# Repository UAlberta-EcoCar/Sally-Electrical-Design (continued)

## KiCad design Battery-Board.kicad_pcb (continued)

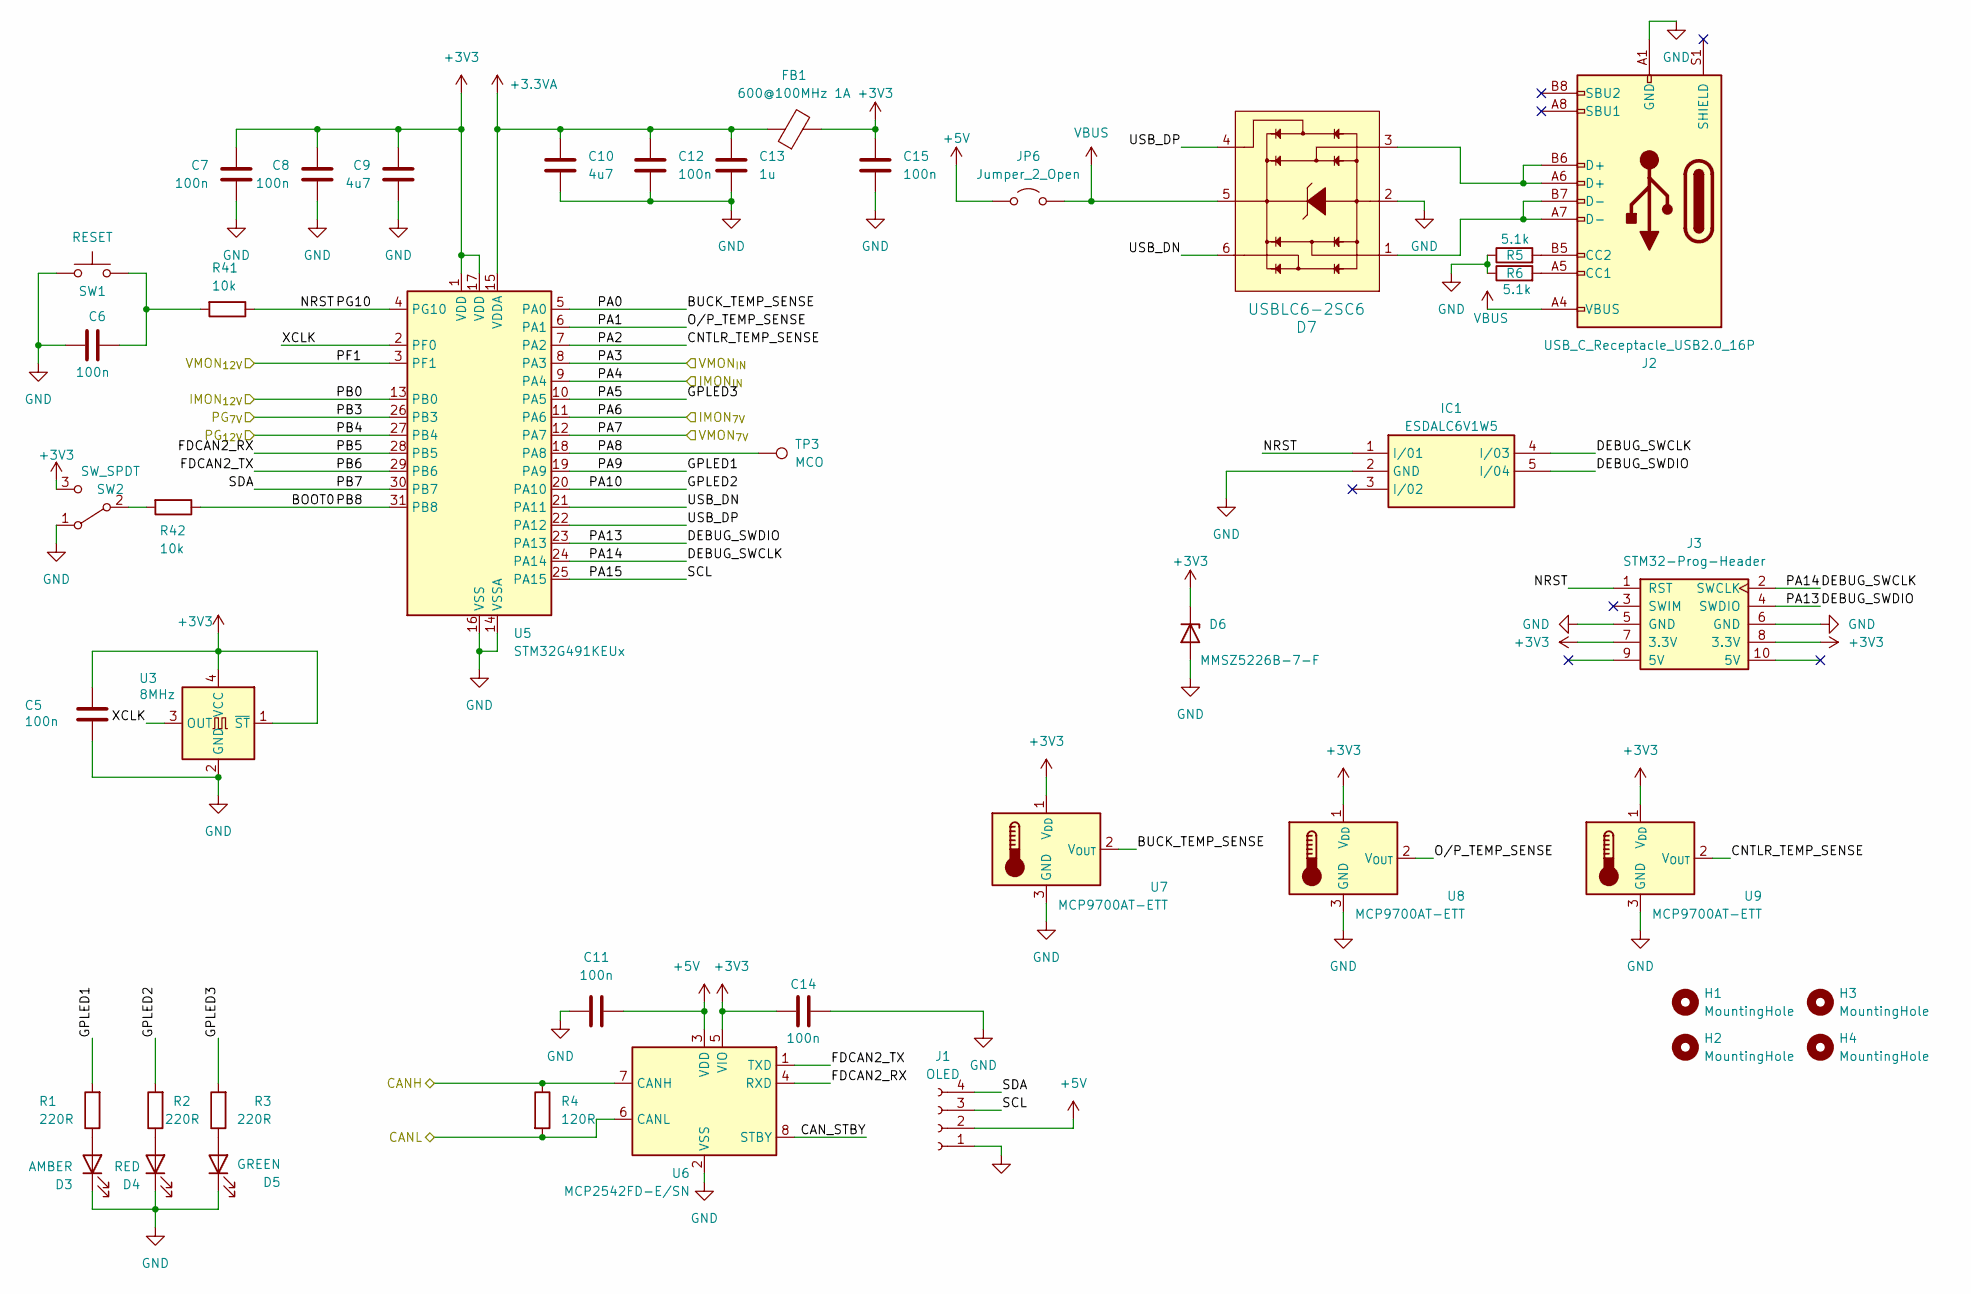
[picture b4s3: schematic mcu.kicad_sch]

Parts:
C5, C6, C11, C14: 100n; C_0603_1608Metric; JLCPCB Part#(Optional) C1525
C7, C8: 100n; C_0603_1608Metric
C9: 4u7; C_0805_2012Metric
C10: 4u7; C_0603_1608Metric; JLCPCB Part#(Optional) C96446
C12: 100n; C_0603_1608Metric; JLCPCB Part#(Optional) C96446
C13: 1u; C_0603_1608Metric; JLCPCB Part#(Optional) C28323
C15: 100n; C_0603_1608Metric; JLCPCB Part#(Optional) C28323
D3: AMBER; LED_0603_1608Metric; JLCPCB Part#(Optional) C2296
D4: RED; LED_0603_1608Metric; JLCPCB Part#(Optional) C84256
D5: GREEN; LED_0603_1608Metric; JLCPCB Part#(Optional) C2297
D6: MMSZ5226B-7-F; D_SOD-123; Digikey # MMSZ5226B-FDICT-ND
D7: USBLC6-2SC6; TSOT-23-6; Digikey # 497-5235-1-ND
FB1: 600@100MHz 1A; L_0603_1608Metric; Digikey # 1934-1474-1-ND
H1, H2, H3, H4: MountingHole; MountingHole_3.5mm
IC1: ESDALC6V1W5; SOT65P210X110-5N; JLCPCB Part#(Optional) C2827626
J1: OLED; Display_128x64_096_I2C
J2: USB_C_Receptacle_USB2.0_16P; USB_C_Receptacle_GCT_USB4105-xx-A_16P_TopMnt_Horizontal
J3: STM32-Prog-Header; PinHeader_2x05_P2.54mm_Vertical
JP6: Jumper_2_Open
R1, R2, R3: 220R; R_0603_1608Metric; JLCPCB Part#(Optional) C17557
R4: 120R; R_0603_1608Metric
R5, R6: 5.1k; R_0603_1608Metric; JLCPCB Part#(Optional) C17557
R41, R42: 10k; R_0603_1608Metric; JLCPCB Part#(Optional) C17557
SW1: RESET; SW_PUSH_6mm_H5mm
SW2: SW_SPDT; SW_SPDT_PCM12; Digikey # 2223-SLW-66527511-SMT-TRCT-ND
TP3: MCO; PinHeader_1x01_P2.54mm_Vertical
U3: 8MHz; Crystal_SMD_3225-4Pin_3.2x2.5mm; Digikey # 535-ASE-8.000MHZ-L-C-TCT-ND
U5: STM32G491KEUx; QFN-32-1EP_5x5mm_P0.5mm_EP3.45x3.45mm
U6: MCP2542FD-E/SN; SOIC-8_3.9x4.9mm_P1.27mm; Digikey # MCP2542FD-E/SN-ND
U7, U8, U9: MCP9700AT-ETT; SOT-23; LCSC# C42288

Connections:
+3.3VA: C10.1, C12.1, C13.1, FB1.1, U5.15 (VDDA)
+3V3: C5.2, C7.1, C8.1, C9.1, C14.2, C15.1, D6.1 (K), FB1.2, J3.7 (3.3V), J3.8 (3.3V), SW2.3 (C), U3.1 (~ST), U3.4 (VCC), U5.1 (VDD), U5.17 (VDD), U6.5 (VIO), U7.1 (V_{DD}), U8.1 (V_{DD}), U9.1 (V_{DD}); also elsewhere on the board
+5V: C11.2, J1.2, JP6.1 (A), U6.3 (VDD); also elsewhere on the board
/CANH: R4.1, U6.7 (CANH); also elsewhere on the board
/CANL: R4.2, U6.6 (CANL); also elsewhere on the board
/MCU and sensors/BUCK_TEMP_SENSE: U5.5 (PA0), U7.2 (V_{OUT})
/MCU and sensors/CAN_STBY: U6.8 (STBY)
/MCU and sensors/CNTLR_TEMP_SENSE: U5.7 (PA2), U9.2 (V_{OUT})
/MCU and sensors/DEBUG_SWCLK: IC1.4 (I/03), J3.2 (SWCLK), U5.24 (PA14)
/MCU and sensors/DEBUG_SWDIO: IC1.5 (I/04), J3.4 (SWDIO), U5.23 (PA13)
/MCU and sensors/FDCAN2_RX: U5.28 (PB5), U6.4 (RXD)
/MCU and sensors/FDCAN2_TX: U5.29 (PB6), U6.1 (TXD)
/MCU and sensors/GPLED1: R1.2, U5.19 (PA9)
/MCU and sensors/GPLED2: R2.2, U5.20 (PA10)
/MCU and sensors/GPLED3: R3.2, U5.10 (PA5)
/MCU and sensors/NRST: IC1.1 (I/01), J3.1 (RST), R41.1, U5.4 (PG10)
/MCU and sensors/O/P_TEMP_SENSE: U5.6 (PA1), U8.2 (V_{OUT})
/MCU and sensors/PA3: U5.8 (PA3); also elsewhere on the board
/MCU and sensors/PA4: U5.9 (PA4); also elsewhere on the board
/MCU and sensors/PA6: U5.11 (PA6); also elsewhere on the board
/MCU and sensors/PA7: U5.12 (PA7); also elsewhere on the board
/MCU and sensors/PA8: TP3.1, U5.18 (PA8)
/MCU and sensors/PA15: J1.3, U5.25 (PA15)
/MCU and sensors/PB0: U5.13 (PB0); also elsewhere on the board
/MCU and sensors/PB3: U5.26 (PB3); also elsewhere on the board
/MCU and sensors/PB4: U5.27 (PB4); also elsewhere on the board
/MCU and sensors/PB7: J1.4, U5.30 (PB7)
/MCU and sensors/PF1: U5.3 (PF1); also elsewhere on the board
/MCU and sensors/USB_DN: D7.6, U5.21 (PA11)
/MCU and sensors/USB_DP: D7.4, U5.22 (PA12)
/MCU and sensors/XCLK: U3.3 (OUT), U5.2 (PF0)
GND: C5.1, C6.1, C7.2, C8.2, C9.2, C10.2, C11.1, C12.2, C13.2, C14.1, C15.2, D3.1 (K), D4.1 (K), D5.1 (K), D6.2 (A), D7.2, IC1.2 (GND), J1.1, J2.A1 (GND), J2.A12 (GND), J2.B1 (GND), J2.B12 (GND), J3.5 (GND), J3.6 (GND), R5.1, R6.1, SW1.1, SW2.1 (A), U3.2 (GND), U5.14 (VSSA), U5.16 (VSS), U5.32 (VSS), U5.33 (VSS), U6.2 (VSS), U6.9 (VSS), U7.3 (GND), U8.3 (GND), U9.3 (GND); also elsewhere on the board
unnamed: C6.2, R41.2, SW1.2
unnamed: D3.2 (A), R1.1
unnamed: D4.2 (A), R2.1
unnamed: D5.2 (A), R3.1
unnamed: D7.1, J2.A7 (D-), J2.B7 (D-)
unnamed: D7.3, J2.A6 (D+), J2.B6 (D+)
unnamed: J2.A5 (CC1), R6.2
unnamed: J2.B5 (CC2), R5.2
unnamed: R42.2, SW2.2 (B)
unnamed: R42.1, U5.31 (PB8)
VBUS: D7.5, J2.A4 (VBUS), J2.A9 (VBUS), J2.B4 (VBUS), J2.B9 (VBUS), JP6.2 (B)

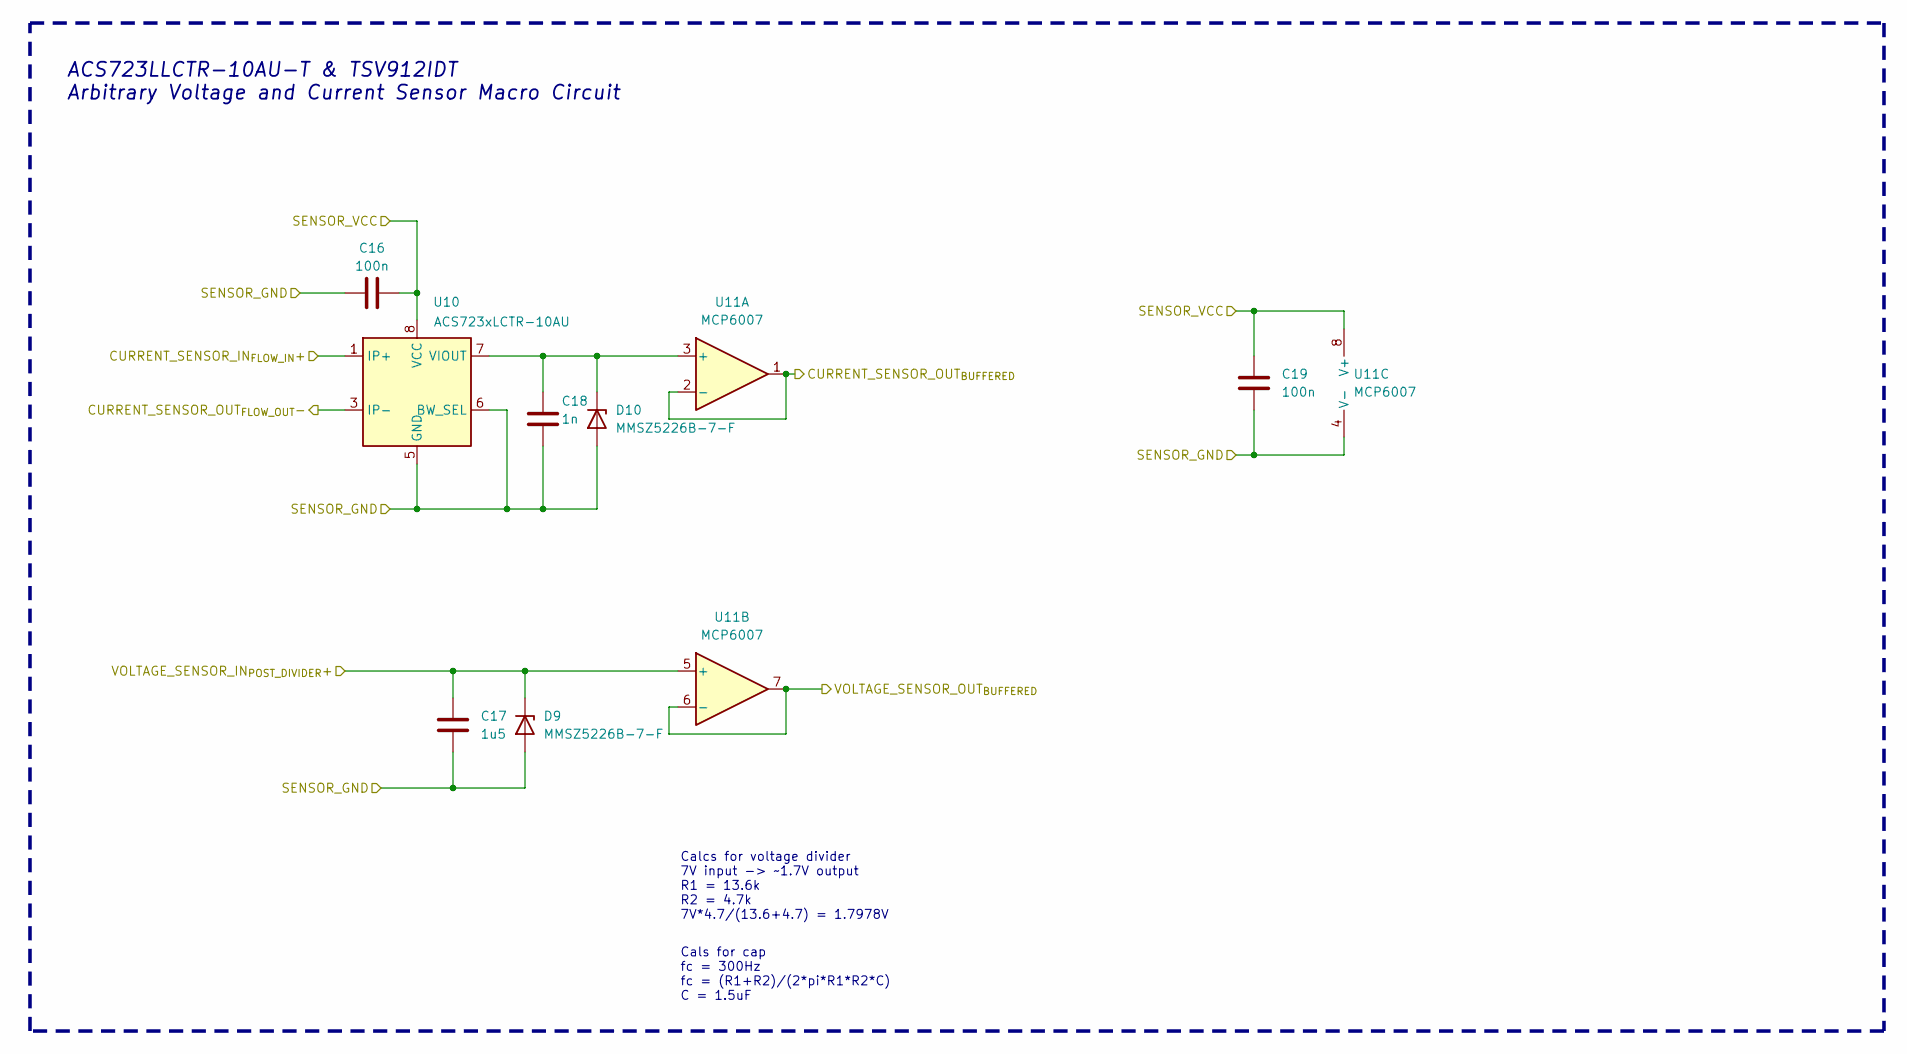
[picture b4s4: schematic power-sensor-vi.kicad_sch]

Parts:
C16, C19: 100n; C_0603_1608Metric; Digikey # CC0603KRX7R7BB104
C17: 1u5; C_0603_1608Metric; JLCPCB Part#(Optional) C28323
C18: 1n; C_0603_1608Metric; JLCPCB Part#(Optional) C1523
D9, D10: MMSZ5226B-7-F; D_SOD-123; Digikey # MMSZ5226B-FDICT-ND
U10: ACS723xLCTR-10AU; SOIC-8_3.9x4.9mm_P1.27mm
U11: MCP6007; SOIC-8_3.9x4.9mm_P1.27mm

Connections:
+5V: C16.1, C19.1, U10.8 (VCC), U11.8 (V+); also elsewhere on the board
/DC-DC-Converters/DC-DC-Buck-Converter2/Output: U10.1 (IP+), U10.2 (IP+); also elsewhere on the board
/DC-DC-Converters/Power Sensor VI2/VOLTAGE_SENSOR_IN_{POST_DIVIDER}+: C17.1, D9.1 (K), U11.5 (+); also elsewhere on the board
/MCU and sensors/PB0: U11.1, U11.2 (-); also elsewhere on the board
/MCU and sensors/PF1: U11.6 (-), U11.7; also elsewhere on the board
/OUT_{12V}: U10.3 (IP-), U10.4 (IP-); also elsewhere on the board
GND: C16.2, C17.2, C18.2, C19.2, D9.2 (A), D10.2 (A), U10.5 (GND), U10.6 (BW_SEL), U11.4 (V-); also elsewhere on the board
unnamed: C18.1, D10.1 (K), U10.7 (VIOUT), U11.3 (+)

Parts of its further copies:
C1, C4, C90, C93: 100n; C_0603_1608Metric; Digikey # CC0603KRX7R7BB104
C2, C91: 1u5; C_0603_1608Metric; JLCPCB Part#(Optional) C28323
C3, C92: 1n; C_0603_1608Metric; JLCPCB Part#(Optional) C1523
D1, D2, D15, D16: MMSZ5226B-7-F; D_SOD-123; Digikey # MMSZ5226B-FDICT-ND
U1, U28: ACS723xLCTR-10AU; SOIC-8_3.9x4.9mm_P1.27mm
U2, U29: MCP6007; SOIC-8_3.9x4.9mm_P1.27mm

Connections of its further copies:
+5V: C1.1, C4.1, C90.1, C93.1, U1.8 (VCC), U2.8 (V+), U28.8 (VCC), U29.8 (V+); also elsewhere on the board
/DC-DC-Converters/DC-DC-Buck-Converter1/Output: U28.1 (IP+), U28.2 (IP+); also elsewhere on the board
/DC-DC-Converters/DC-DC-Buck-Converter2/POWER_IN: U1.3 (IP-), U1.4 (IP-); also elsewhere on the board
/DC-DC-Converters/Power Sensor VI1/VOLTAGE_SENSOR_IN_{POST_DIVIDER}+: C2.1, D1.1 (K), U2.5 (+); also elsewhere on the board
/DC-DC-Converters/Power Sensor VI4/VOLTAGE_SENSOR_IN_{POST_DIVIDER}+: C91.1, D15.1 (K), U29.5 (+); also elsewhere on the board
/IN_{24V}: U1.1 (IP+), U1.2 (IP+); also elsewhere on the board
/MCU and sensors/PA3: U2.6 (-), U2.7; also elsewhere on the board
/MCU and sensors/PA4: U2.1, U2.2 (-); also elsewhere on the board
/MCU and sensors/PA6: U29.1, U29.2 (-); also elsewhere on the board
/MCU and sensors/PA7: U29.6 (-), U29.7; also elsewhere on the board
/OUT_{7V}: U28.3 (IP-), U28.4 (IP-); also elsewhere on the board
GND: C1.2, C2.2, C3.2, C4.2, C90.2, C91.2, C92.2, C93.2, D1.2 (A), D2.2 (A), D15.2 (A), D16.2 (A), U1.5 (GND), U1.6 (BW_SEL), U2.4 (V-), U28.5 (GND), U28.6 (BW_SEL), U29.4 (V-); also elsewhere on the board
unnamed: C3.1, D2.1 (K), U1.7 (VIOUT), U2.3 (+)
unnamed: C92.1, D16.1 (K), U28.7 (VIOUT), U29.3 (+)

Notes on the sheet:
ACS723LLCTR-10AU-T & TSV912IDT Arbitrary Voltage and Current Sensor Macro Circuit
Cals for cap fc = 300Hz fc = (R1+R2)/(2*pi*R1*R2*C) C = 1.5uF
Calcs for voltage divider 7V input -> ~1.7V output R1 = 13.6k R2 = 4.7k 7V*4.7/(13.6+4.7) = 1.7978V

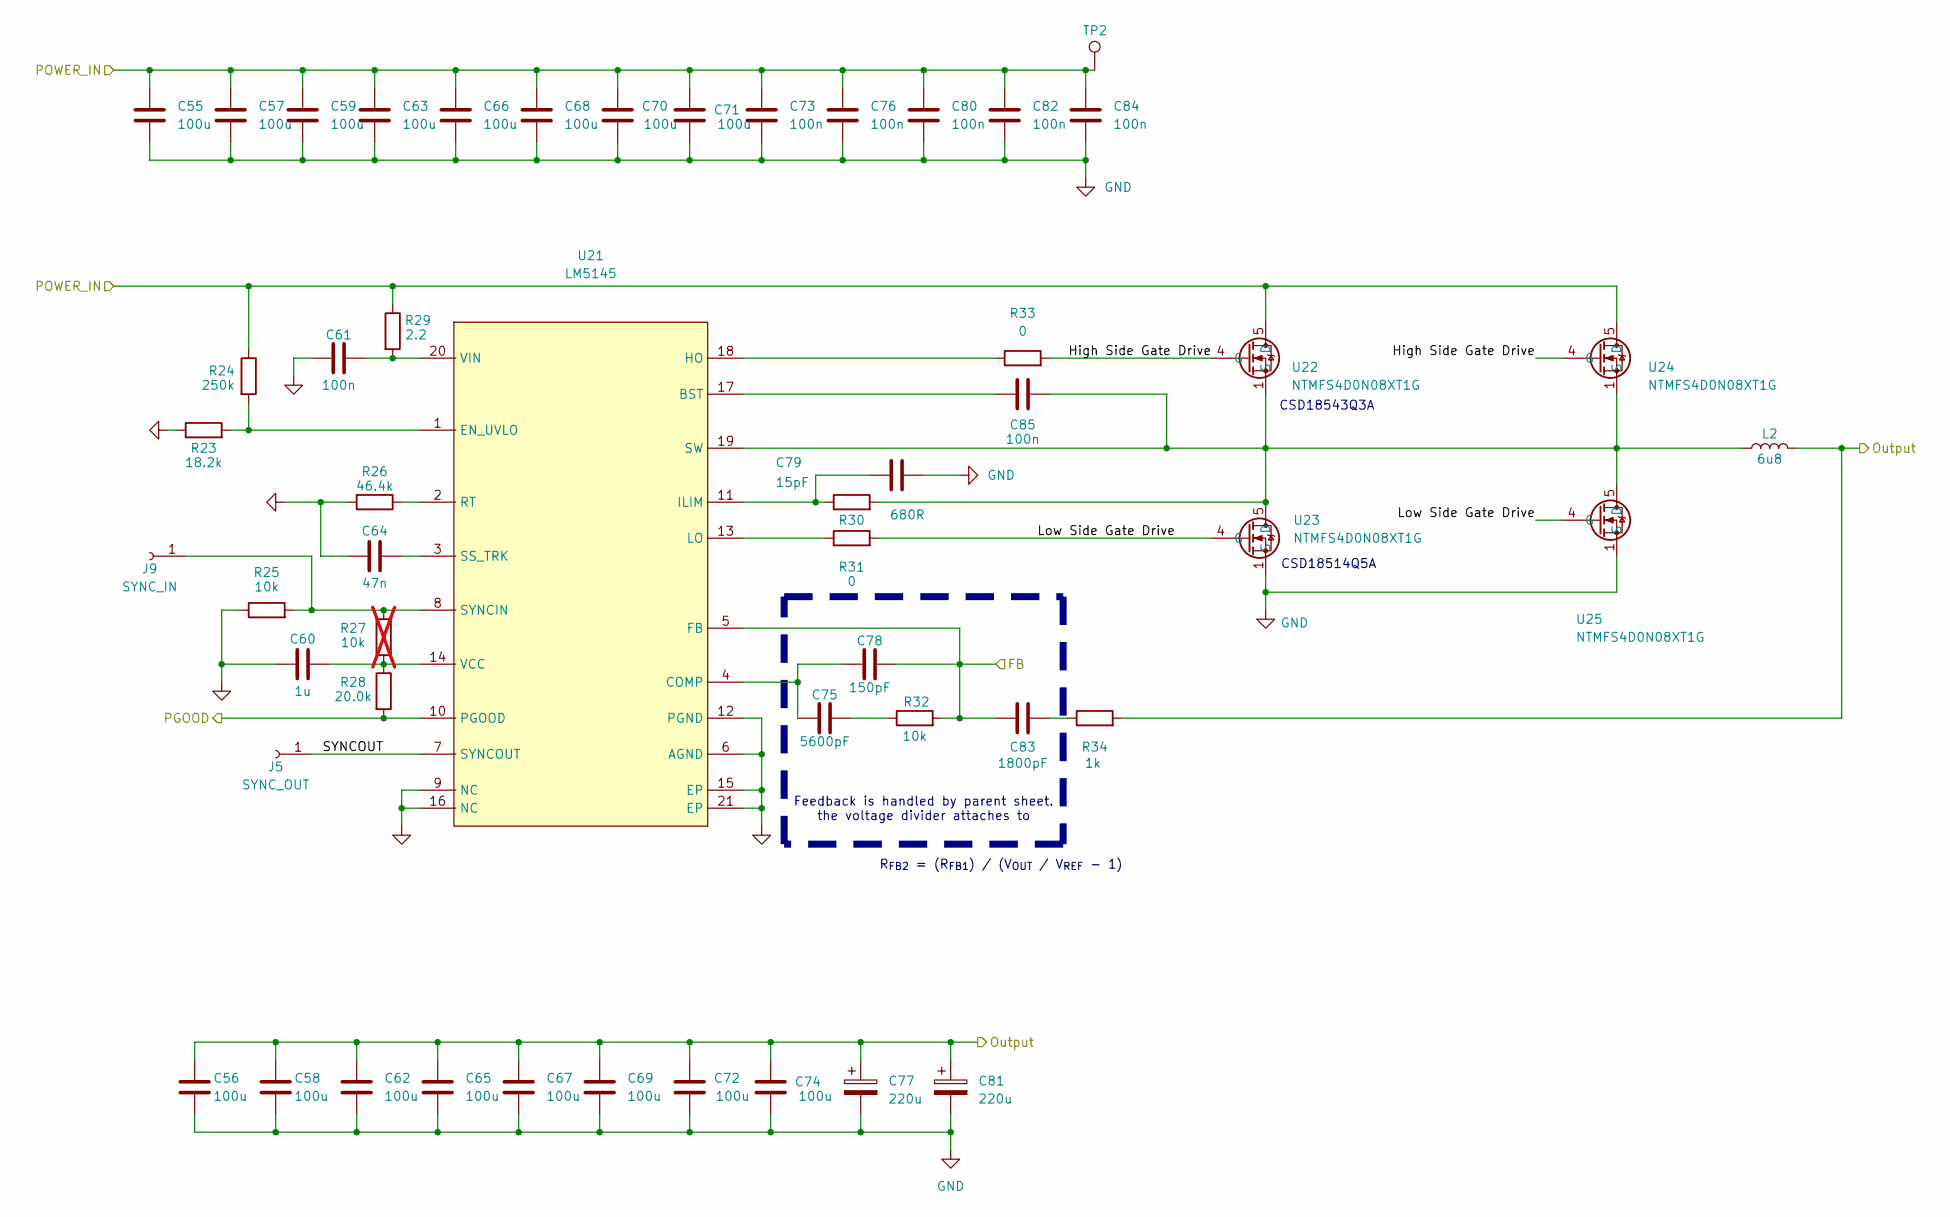
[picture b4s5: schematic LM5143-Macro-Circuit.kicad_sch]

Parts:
C55, C56, C57, C58, C59, C62, C63, C65, C66, C67, C68, C69, C70, C71, C72, C74: 100u; C_1210_3225Metric
C60: 1u; C_0603_1608Metric
C61, C73, C76, C80, C82, C84, C85: 100n; C_0603_1608Metric
C64: 47n; C_0603_1608Metric
C75: 5600pF; C_0603_1608Metric
C77, C81: 220u; CAP_EEE1HA221P
C78: 150pF; C_0603_1608Metric
C79: 15pF; C_0603_1608Metric
C83: 1800pF; C_0603_1608Metric
J5: SYNC_OUT; PinHeader_1x01_P2.54mm_Vertical
J9: SYNC_IN; PinHeader_1x01_P2.54mm_Vertical
L2: 6u8; L_Bourns_SRR1208_12.7x12.7mm
R23: 18.2k; R_0603_1608Metric
R24: 250k; R_0603_1608Metric
R25, R32: 10k; R_0603_1608Metric
R26: 46.4k; R_0603_1608Metric
R27: 10k; R_0603_1608Metric; not fitted
R28: 20.0k; R_0603_1608Metric
R29: 2.2; R_0603_1608Metric
R30: 680R; R_0603_1608Metric
R31, R33: 0; R_0603_1608Metric
R34: 1k; R_0603_1608Metric
TP2: TestPoint; PinHeader_1x01_P2.54mm_Vertical
U21: LM5145; Texas_RGY_R-PVQFN-N20_EP2.05x3.05mm_ThermalVias
U22, U23, U24, U25: NTMFS4D0N08XT1G; PowerMosDFNHybrid

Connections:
/DC-DC-Converters/DC-DC-Buck-Converter2/FB: C78.2, C83.1, R32.2, U21.5 (FB); also elsewhere on the board
/DC-DC-Converters/DC-DC-Buck-Converter2/High Side Gate Drive: R33.2, U22.4 (G), U24.4 (G)
/DC-DC-Converters/DC-DC-Buck-Converter2/Low Side Gate Drive: R31.2, U23.4 (G), U25.4 (G)
/DC-DC-Converters/DC-DC-Buck-Converter2/Output: C56.1, C58.1, C62.1, C65.1, C67.1, C69.1, C72.1, C74.1, C77.1, C81.1, L2.2, R34.2; also elsewhere on the board
/DC-DC-Converters/DC-DC-Buck-Converter2/POWER_IN: C55.1, C57.1, C59.1, C63.1, C66.1, C68.1, C70.1, C71.1, C73.1, C76.1, C80.1, C82.1, C84.1, R24.1, R29.1, TP2.1, U22.5 (D), U24.5 (D); also elsewhere on the board
/DC-DC-Converters/DC-DC-Buck-Converter2/SYNCOUT: J5.1, U21.7 (SYNCOUT)
/MCU and sensors/PB4: R28.2, U21.10 (PGOOD); also elsewhere on the board
GND: C55.2, C56.2, C57.2, C58.2, C59.2, C60.1, C61.1, C62.2, C63.2, C64.1, C65.2, C66.2, C67.2, C68.2, C69.2, C70.2, C71.2, C72.2, C73.2, C74.2, C76.2, C77.2, C79.1, C80.2, C81.2, C82.2, C84.2, R23.1, R25.1, R26.2, U21.6 (AGND), U21.9 (NC), U21.12 (PGND), U21.15 (EP), U21.16 (NC), U21.21 (EP), U23.1 (S), U23.2 (S), U23.3 (S), U25.1 (S), U25.2 (S), U25.3 (S); also elsewhere on the board
unnamed: C75.2, R32.1
unnamed: C83.2, R34.1
unnamed: J9.1, R25.2, R27.1, U21.8 (SYNCIN)
unnamed: C85.2, U21.17 (BST)
unnamed: C75.1, C78.1, U21.4 (COMP)
unnamed: R23.2, R24.2, U21.1 (EN_UVLO)
unnamed: R33.1, U21.18 (HO)
unnamed: C79.2, R30.1, U21.11 (ILIM)
unnamed: R31.1, U21.13 (LO)
unnamed: R26.1, U21.2 (RT)
unnamed: C64.2, U21.3 (SS_TRK)
unnamed: C85.1, L2.1, R30.2, U21.19 (SW), U22.1 (S), U22.2 (S), U22.3 (S), U23.5 (D), U24.1 (S), U24.2 (S), U24.3 (S), U25.5 (D)
unnamed: C60.2, R27.2, R28.1, U21.14 (VCC)
unnamed: C61.2, R29.2, U21.20 (VIN)

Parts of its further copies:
C20, C21, C22, C23, C24, C27, C28, C30, C31, C32, C33, C34, C35, C36, C37, C39: 100u; C_1210_3225Metric
C25: 1u; C_0603_1608Metric
C26, C38, C41, C45, C47, C49, C50: 100n; C_0603_1608Metric
C29: 47n; C_0603_1608Metric
C40: 5600pF; C_0603_1608Metric
C42, C46: 220u; CAP_EEE1HA221P
C43: 150pF; C_0603_1608Metric
C44: 15pF; C_0603_1608Metric
C48: 1800pF; C_0603_1608Metric
J4: SYNC_OUT; PinHeader_1x01_P2.54mm_Vertical
J8: SYNC_IN; PinHeader_1x01_P2.54mm_Vertical
L1: 6u8; L_Bourns_SRR1208_12.7x12.7mm
R11: 18.2k; R_0603_1608Metric
R12: 250k; R_0603_1608Metric
R13, R20: 10k; R_0603_1608Metric
R14: 46.4k; R_0603_1608Metric
R15: 10k; R_0603_1608Metric; not fitted
R16: 20.0k; R_0603_1608Metric
R17: 2.2; R_0603_1608Metric
R18: 680R; R_0603_1608Metric
R19, R21: 0; R_0603_1608Metric
R22: 1k; R_0603_1608Metric
TP1: TestPoint; PinHeader_1x01_P2.54mm_Vertical
U12: LM5145; Texas_RGY_R-PVQFN-N20_EP2.05x3.05mm_ThermalVias
U13, U14, U15, U16: NTMFS4D0N08XT1G; PowerMosDFNHybrid

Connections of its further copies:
/DC-DC-Converters/DC-DC-Buck-Converter1/FB: C43.2, C48.1, R20.2, U12.5 (FB); also elsewhere on the board
/DC-DC-Converters/DC-DC-Buck-Converter1/High Side Gate Drive: R21.2, U13.4 (G), U15.4 (G)
/DC-DC-Converters/DC-DC-Buck-Converter1/Low Side Gate Drive: R19.2, U14.4 (G), U16.4 (G)
/DC-DC-Converters/DC-DC-Buck-Converter1/Output: C21.1, C23.1, C27.1, C30.1, C32.1, C34.1, C37.1, C39.1, C42.1, C46.1, L1.2, R22.2; also elsewhere on the board
/DC-DC-Converters/DC-DC-Buck-Converter1/POWER_IN: C20.1, C22.1, C24.1, C28.1, C31.1, C33.1, C35.1, C36.1, C38.1, C41.1, C45.1, C47.1, C49.1, R12.1, R17.1, TP1.1, U13.5 (D), U15.5 (D); also elsewhere on the board
/DC-DC-Converters/DC-DC-Buck-Converter1/SYNCOUT: J4.1, U12.7 (SYNCOUT)
/MCU and sensors/PB3: R16.2, U12.10 (PGOOD); also elsewhere on the board
GND: C20.2, C21.2, C22.2, C23.2, C24.2, C25.1, C26.1, C27.2, C28.2, C29.1, C30.2, C31.2, C32.2, C33.2, C34.2, C35.2, C36.2, C37.2, C38.2, C39.2, C41.2, C42.2, C44.1, C45.2, C46.2, C47.2, C49.2, R11.1, R13.1, R14.2, U12.6 (AGND), U12.9 (NC), U12.12 (PGND), U12.15 (EP), U12.16 (NC), U12.21 (EP), U14.1 (S), U14.2 (S), U14.3 (S), U16.1 (S), U16.2 (S), U16.3 (S); also elsewhere on the board
unnamed: C40.2, R20.1
unnamed: C48.2, R22.1
unnamed: J8.1, R13.2, R15.1, U12.8 (SYNCIN)
unnamed: C50.2, U12.17 (BST)
unnamed: C40.1, C43.1, U12.4 (COMP)
unnamed: R11.2, R12.2, U12.1 (EN_UVLO)
unnamed: R21.1, U12.18 (HO)
unnamed: C44.2, R18.1, U12.11 (ILIM)
unnamed: R19.1, U12.13 (LO)
unnamed: R14.1, U12.2 (RT)
unnamed: C29.2, U12.3 (SS_TRK)
unnamed: C50.1, L1.1, R18.2, U12.19 (SW), U13.1 (S), U13.2 (S), U13.3 (S), U14.5 (D), U15.1 (S), U15.2 (S), U15.3 (S), U16.5 (D)
unnamed: C25.2, R15.2, R16.1, U12.14 (VCC)
unnamed: C26.2, R17.2, U12.20 (VIN)

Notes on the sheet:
CSD18514Q5A
CSD18543Q3A
Feedback is handled by parent sheet. the voltage divider attaches to
R_{FB2} = (R_{FB1}) / (V_{OUT} / V_{REF} - 1)

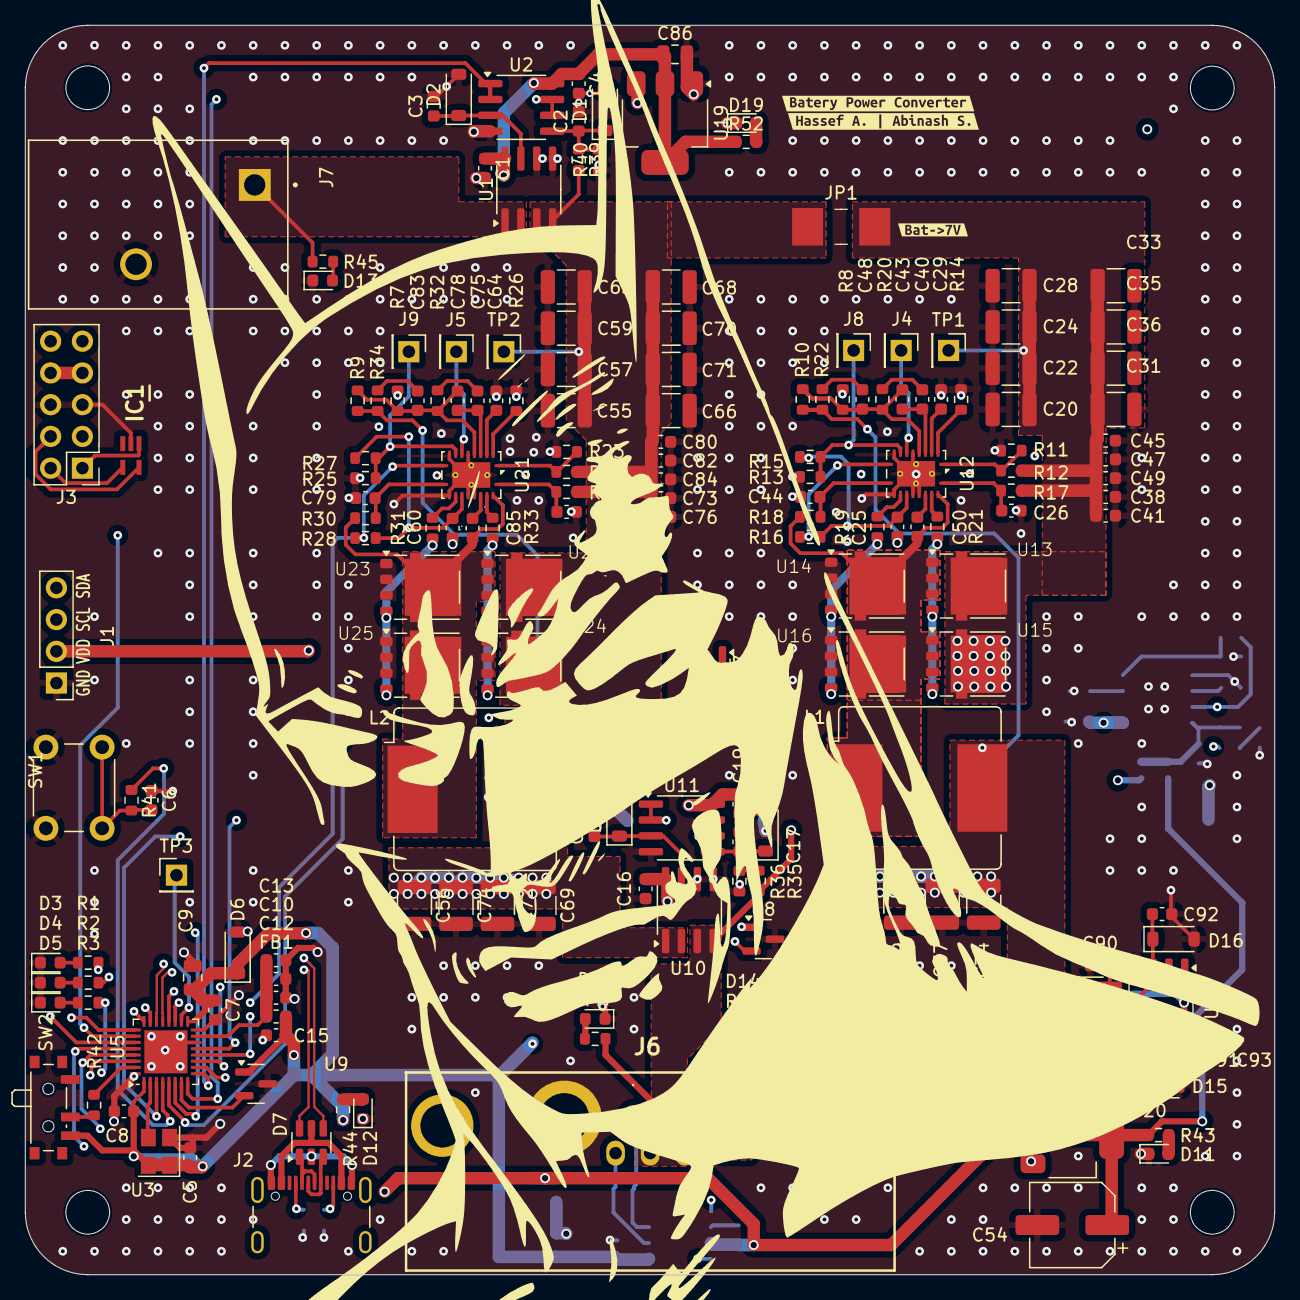
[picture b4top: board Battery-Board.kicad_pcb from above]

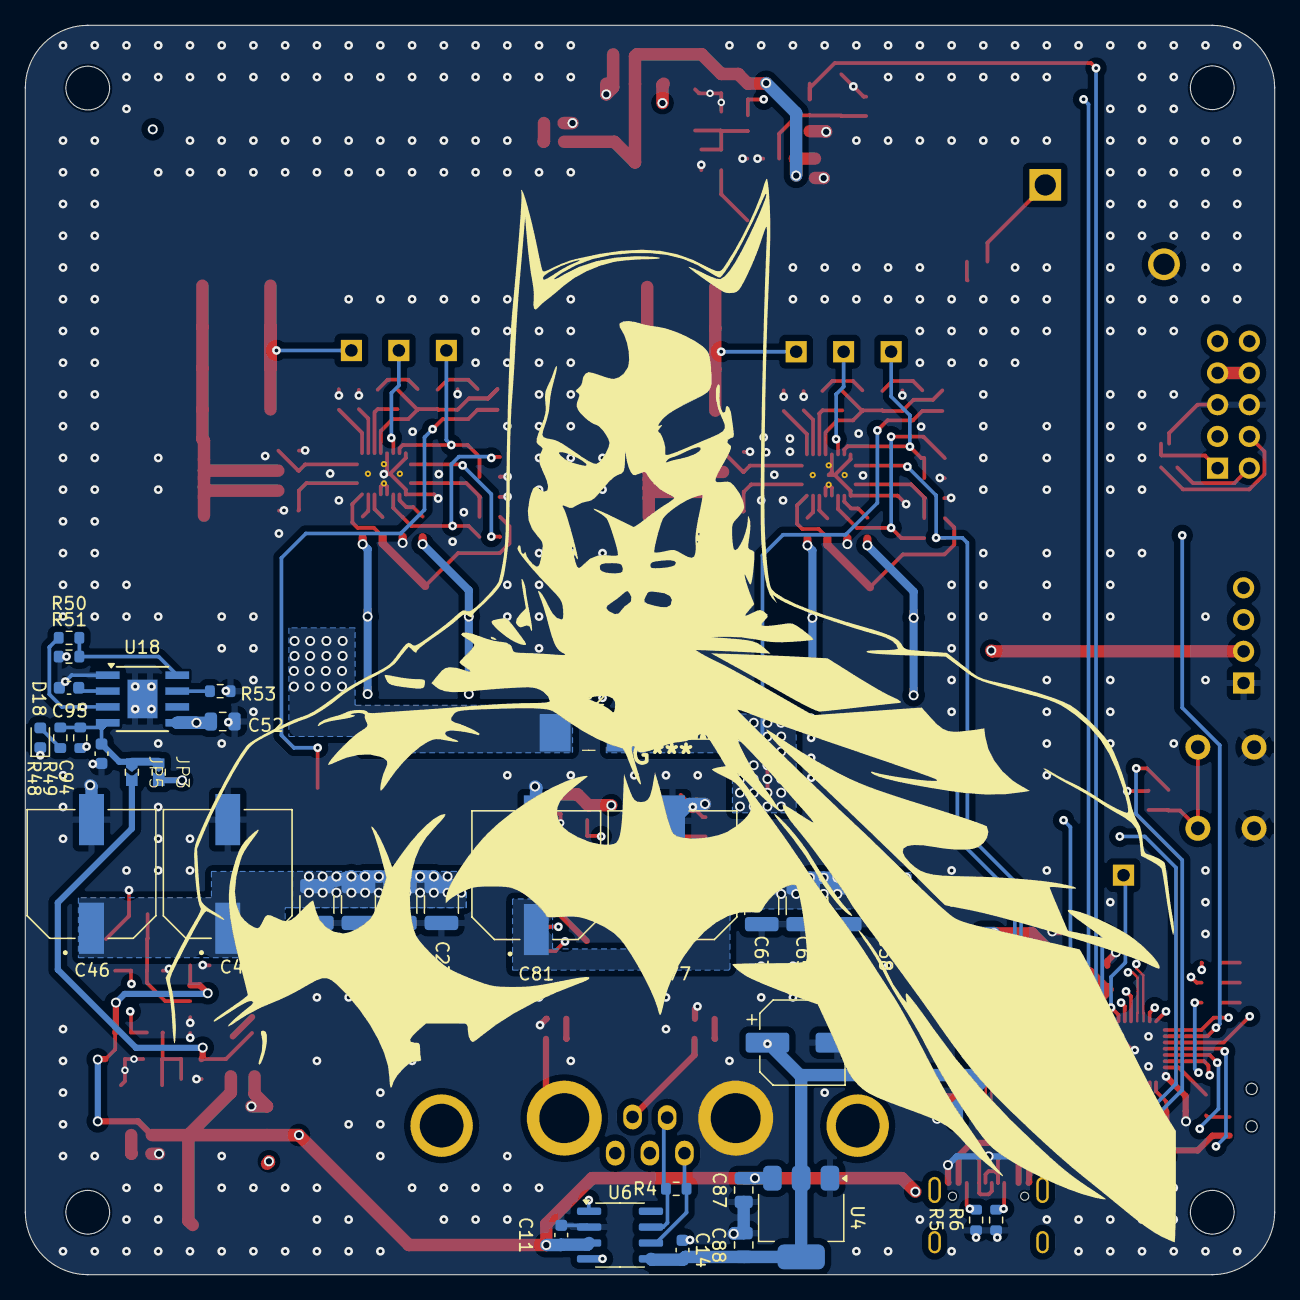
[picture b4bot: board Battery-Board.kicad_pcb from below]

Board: 4 copper layers, 100.0 x 100.0 mm, 221 parts (36 on the bottom side), 104 nets.

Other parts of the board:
kibuzzard-6785F55D: G***; kibuzzard-6785F55D
kibuzzard-6785F57A: G***; kibuzzard-6785F57A
kibuzzard-67848C10: G***; kibuzzard-67848C10
kibuzzard-67848C36: G***; kibuzzard-67848C36

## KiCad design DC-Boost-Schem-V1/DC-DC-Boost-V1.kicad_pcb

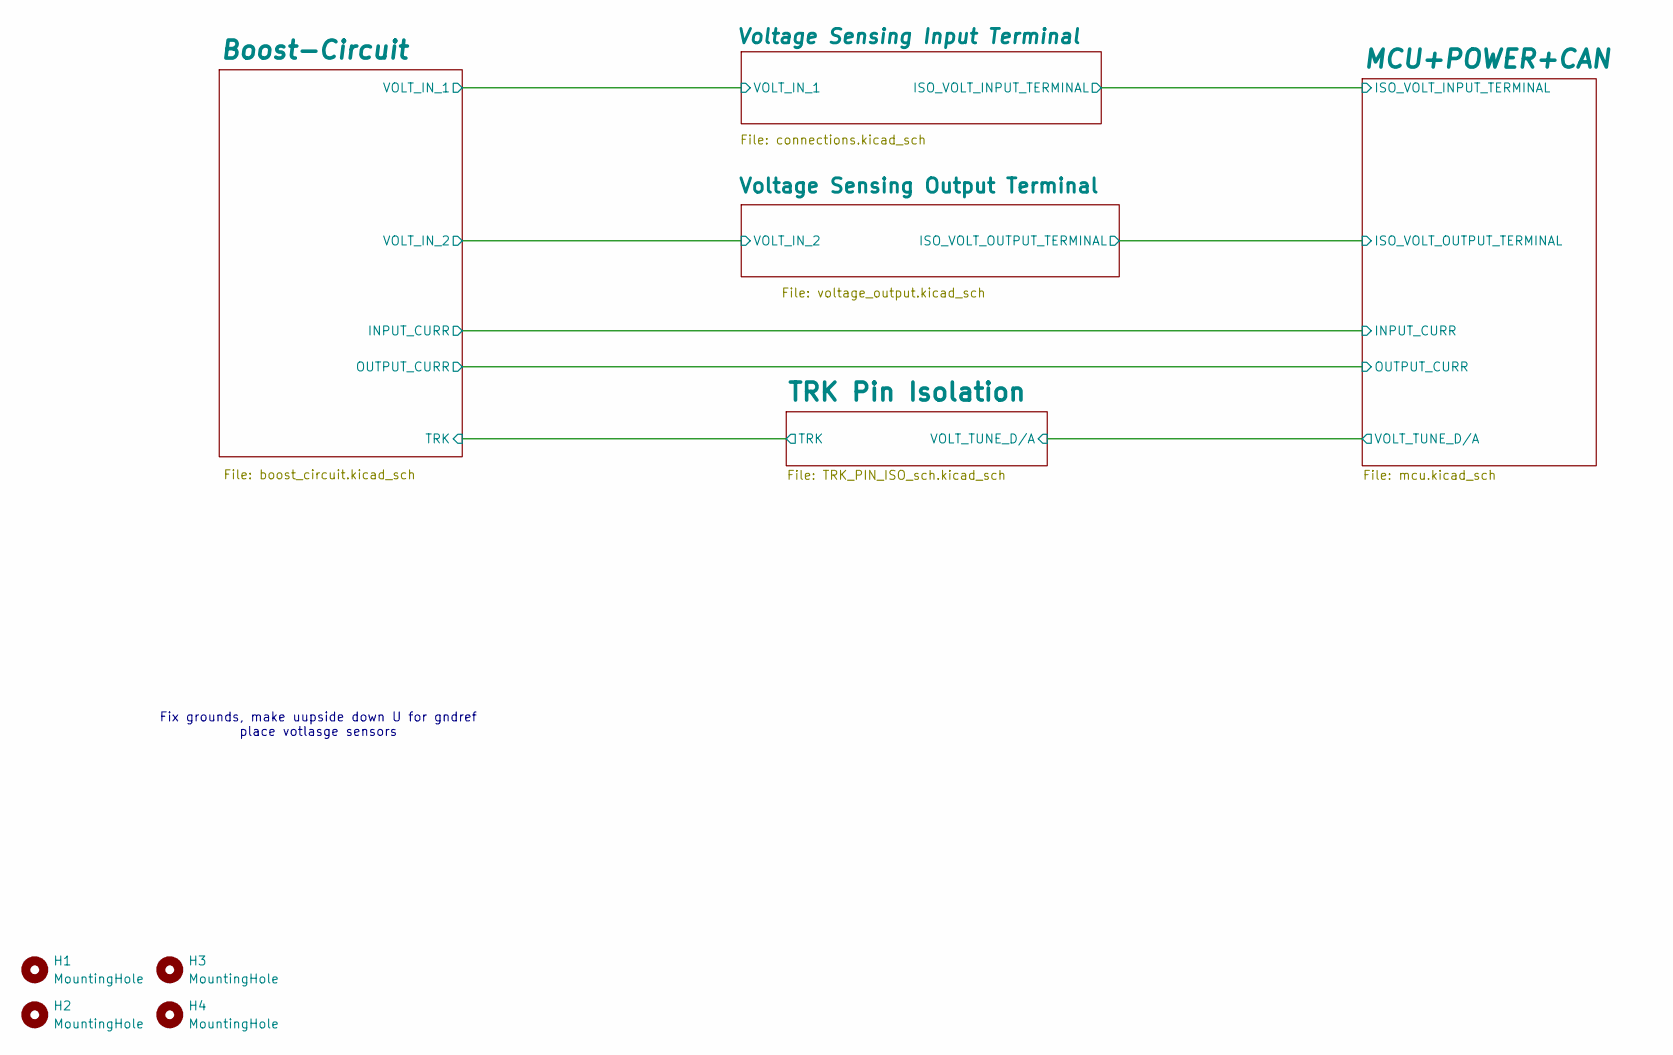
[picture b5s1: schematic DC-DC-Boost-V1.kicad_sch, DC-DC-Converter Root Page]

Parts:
H1, H2, H3, H4: MountingHole; MountingHole_3.5mm

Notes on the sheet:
Fix grounds, make uupside down U for gndref place votlasge sensors
